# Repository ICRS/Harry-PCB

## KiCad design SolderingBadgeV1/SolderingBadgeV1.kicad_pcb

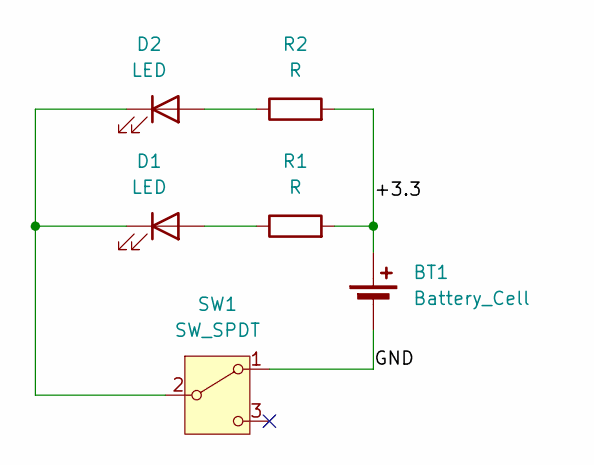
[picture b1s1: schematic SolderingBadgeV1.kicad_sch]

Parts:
BT1: Battery_Cell; BatteryHolder_Multicomp_BC-2001_1x2032
D1, D2: LED; LED_D3.0mm
R1, R2: R; R_Axial_DIN0207_L6.3mm_D2.5mm_P7.62mm_Horizontal
SW1: SW_SPDT; SW_Slide-03_Wuerth-WS-SLTV_10x2.5x6.4_P2.54mm

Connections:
/+3.3: BT1.1 (+), R1.2, R2.2
/GND: BT1.2 (-), SW1.1 (A)
unnamed: D1.2 (A), R1.1
unnamed: D1.1 (K), D2.1 (K), SW1.2 (B)
unnamed: D2.2 (A), R2.1

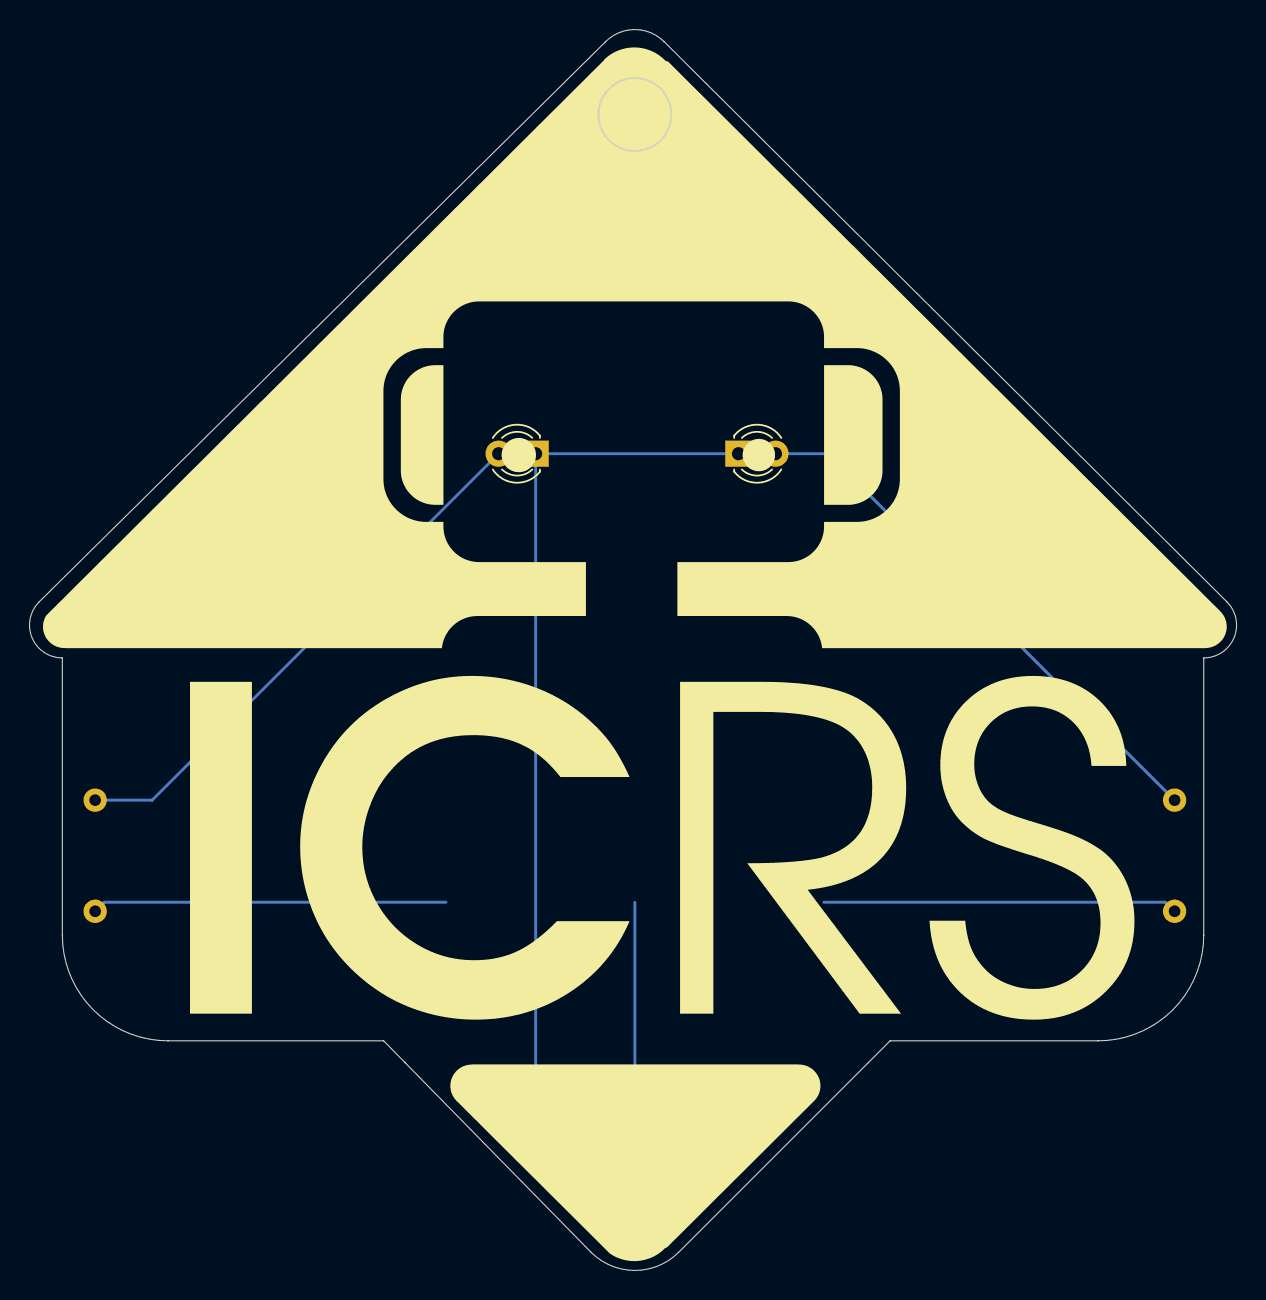
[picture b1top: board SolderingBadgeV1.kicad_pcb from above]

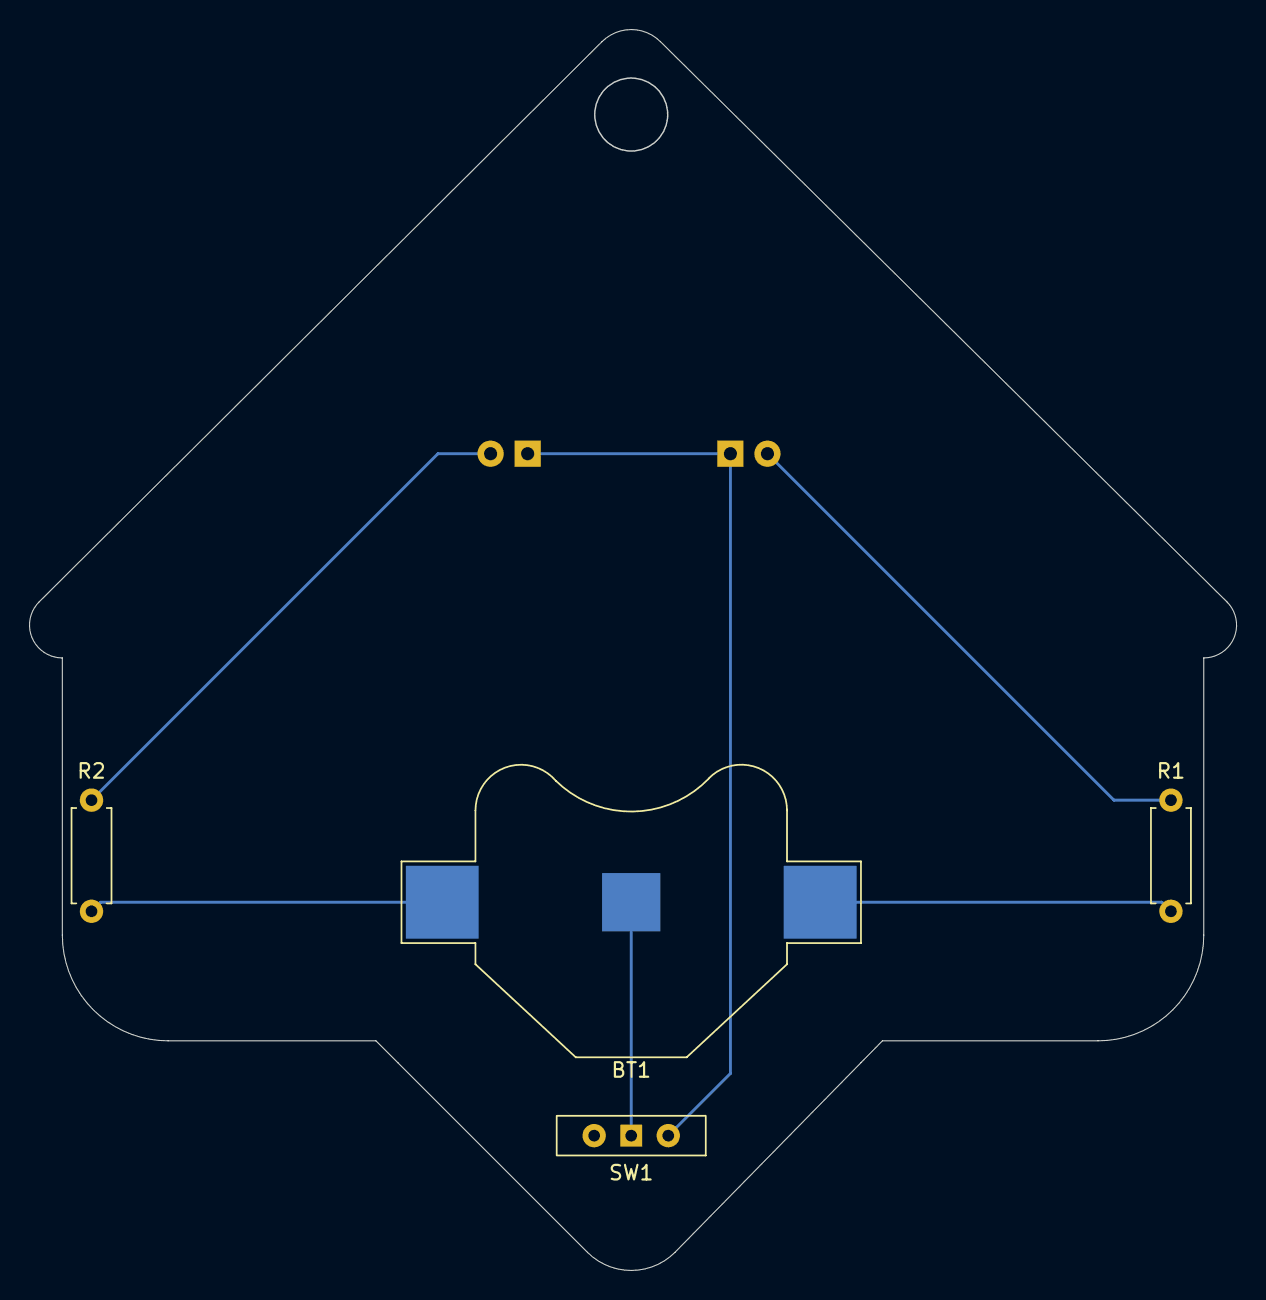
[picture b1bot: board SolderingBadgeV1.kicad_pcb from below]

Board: 2 copper layers, 82.7 x 85.0 mm, 6 parts (4 on the bottom side), 5 nets.

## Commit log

2025-09-06 Added gitignore
2025-09-08 Initial draft without modified board outline
2025-09-08 Formal first draft
2025-09-08 Small changes
    Removed labels for LEDs
    Added keyring hole
    Changed silkscreen colour
2025-09-10 Minor Polishes
2025-09-10 Flipped switch to other side
    just allows silkscreen for switch to be seen
2025-09-10 Harry Badge PCB V1
